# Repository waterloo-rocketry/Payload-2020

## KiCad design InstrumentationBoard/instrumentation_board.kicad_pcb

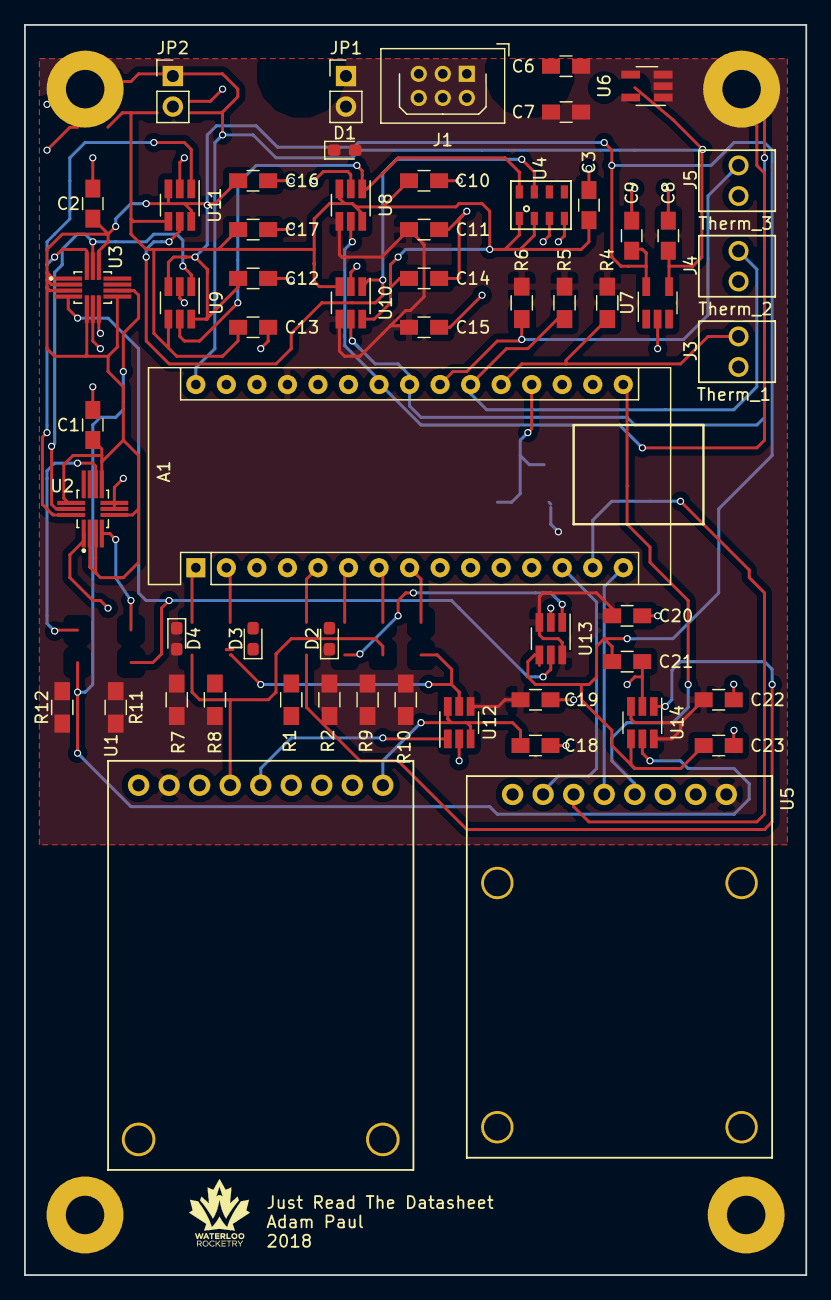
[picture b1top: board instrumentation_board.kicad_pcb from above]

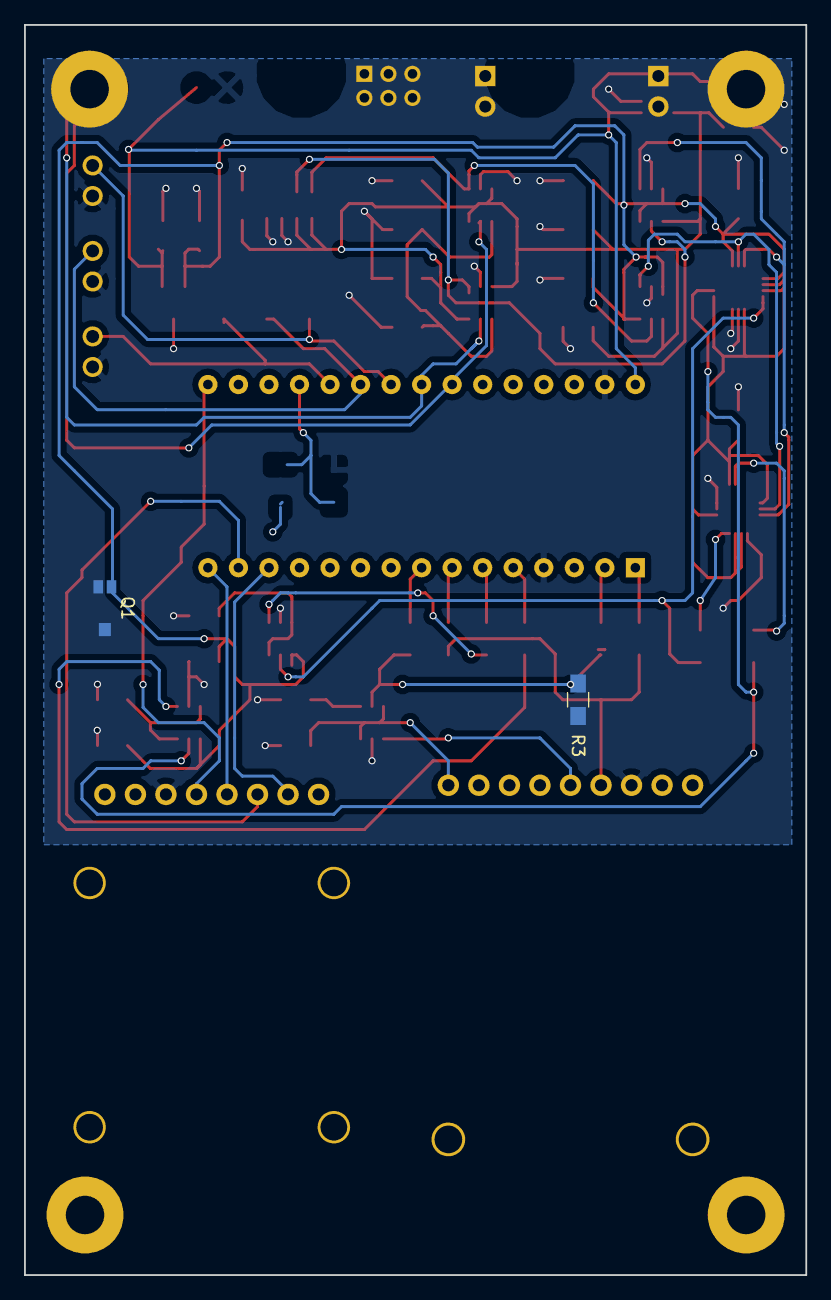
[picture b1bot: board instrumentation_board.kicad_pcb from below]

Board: 2 copper layers, 65.0 x 104.0 mm, 59 parts (2 on the bottom side), 39 nets.

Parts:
A1: Arduino_Nano
C1, C2, C3: 100nF; C_0805_HandSoldering
C6, C7: C; C_0805_HandSoldering
C8: 0.1uF; C_0805_HandSoldering
C9: 0.47uF; C_0805_HandSoldering
C10, C11, C12, C13, C14, C15, C16, C17, C18, C19, C20, C21, C22, C23: .1uF; C_0805_HandSoldering
D1, D2, D3, D4: LED; D_0603_1608Metric_Pad1.05x0.95mm_HandSolder
J1: Conn_01x06; Harwin_LTek-Male_2x03_P2.00mm_Vertical
J3, J4, J5: Conn_01x02; molex_kk_22-23-2021
JP1, JP2: Jumper; PinHeader_1x02_P2.54mm_Vertical
Q1: TEMT6000X01
R1, R2, R3, R7: 120; R_0805_HandSoldering
R4, R5, R6: R; R_0805_HandSoldering
R8, R9, R10: 0; R_0805_HandSoldering
R11, R12: 470; R_0805_HandSoldering
U1: LSM303AGR; gps746
U2, U3: LSM6DS3HTR; LGA-14
U4: MS5607-02BA03; 8-SMD
U5: MicroSD-ADAFRUIT254; adafruit254
U6: XC6201P302MR-G; SOT-23-5_HandSoldering
U7: TPS71518DCKR; SOT-23-5_HandSoldering
U8, U9, U10, U11, U12, U13, U14: PI4ULS5V201TAEX; SOT-23-6_Handsoldering

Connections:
1.8V: C1.1, C2.1, C7.1, C9.1, C12.1, C16.1, C21.1, C23.1, J1.2, R1.2, U1.2, U1.3, U1.9, U2.2, U2.3, U2.5, U2.8, U2.12, U3.1, U3.2, U3.3, U3.5, U3.8, U3.12, U7.5, U9.3, U9.6, U11.3, U11.6, U13.4, U14.4
3V: C3.1, C10.1, C13.1, C14.1, C17.1, J1.3, R2.2, U4.1, U4.2, U6.5, U8.3, U8.6, U9.4, U10.3, U10.6, U11.4
5V: A1.27, C11.1, C15.1, C19.1, C20.1, C22.1, J1.4, Q1.1, R3.2, R4.1, R5.1, R6.1, U5.1, U8.4, U10.4, U12.4, U13.3, U13.6, U14.3, U14.6
7.4V: C8.1, U6.1, U7.4
/ICShifter7/VccA: C18.1, U12.3, U12.6
/Sheet5ABF9899/THERM_OUT: A1.21, J4.2, R5.2
/Sheet5ABF9899_2/THERM_OUT: A1.20, J3.2, R4.2
/Sheet5ABF9899_3/THERM_OUT: A1.22, J5.2, R6.2
GND: A1.4, A1.29, C1.2, C2.2, C3.2, C6.2, C7.2, C8.2, C9.2, C10.2, C11.2, C12.2, C13.2, C14.2, C15.2, C16.2, C17.2, C18.2, C19.2, C20.2, C21.2, C22.2, C23.2, D1.1, D2.1, D3.1, D4.1, J1.1, J3.1, J4.1, J5.1, U1.6, U1.8, U2.1, U2.6, U2.7, U3.6, U3.7, U4.3, U4.4, U5.3, U6.2, U7.2, U8.2, U9.2, U10.2, U11.2, U12.2, U13.2, U14.2
GPS_OUT: R8.1, R10.1, U12.5
INIT_MAG: A1.12, U1.7
INT0_1.8V: R11.1, U3.4, U13.5
INT0_5V: JP2.1, U13.1
INT1_1.8V: R12.2, U3.9, U14.5
INT1_5V: JP1.2, U14.1
MISO: A1.15, U5.5
MOSI: A1.14, U5.6
unnamed: A1.2, R8.2
unnamed: A1.5, JP1.1
unnamed: A1.6, JP2.2
unnamed: A1.7, R9.2
unnamed: A1.8, R10.2
unnamed: A1.11, R7.2
unnamed: C6.1, U1.5
unnamed: D1.2, R1.1
unnamed: D2.2, R2.1
unnamed: D3.2, R3.1
unnamed: D4.2, R7.1
unnamed: R11.2, U2.4
unnamed: R12.1, U2.9
SCL_1.8V: U1.1, U2.13, U3.13, U9.1
SCL_3V: U4.8, U8.1, U9.5
SCL_5V: A1.24, J1.5, U8.5
SDA_1.8V: U1.4, U2.14, U3.14, U11.1
SDA_3V: U4.7, U10.1, U11.5
SDA_5V: A1.23, J1.6, U10.5
SIG: A1.19, Q1.2
SLK: A1.16, U5.4
SS: A1.13, U5.7

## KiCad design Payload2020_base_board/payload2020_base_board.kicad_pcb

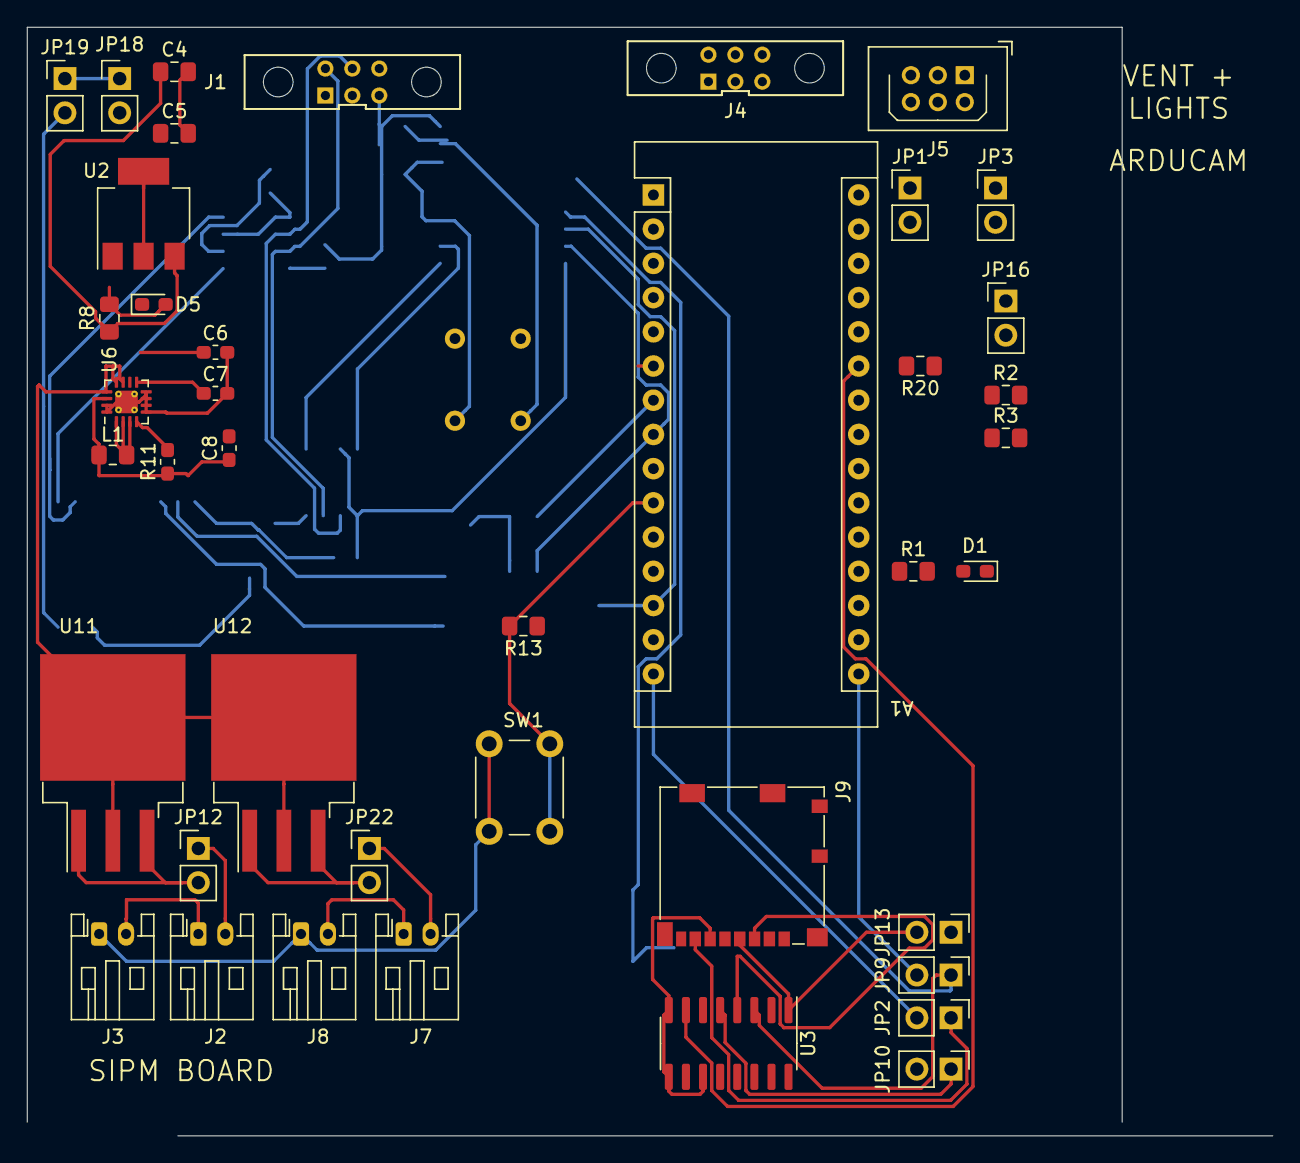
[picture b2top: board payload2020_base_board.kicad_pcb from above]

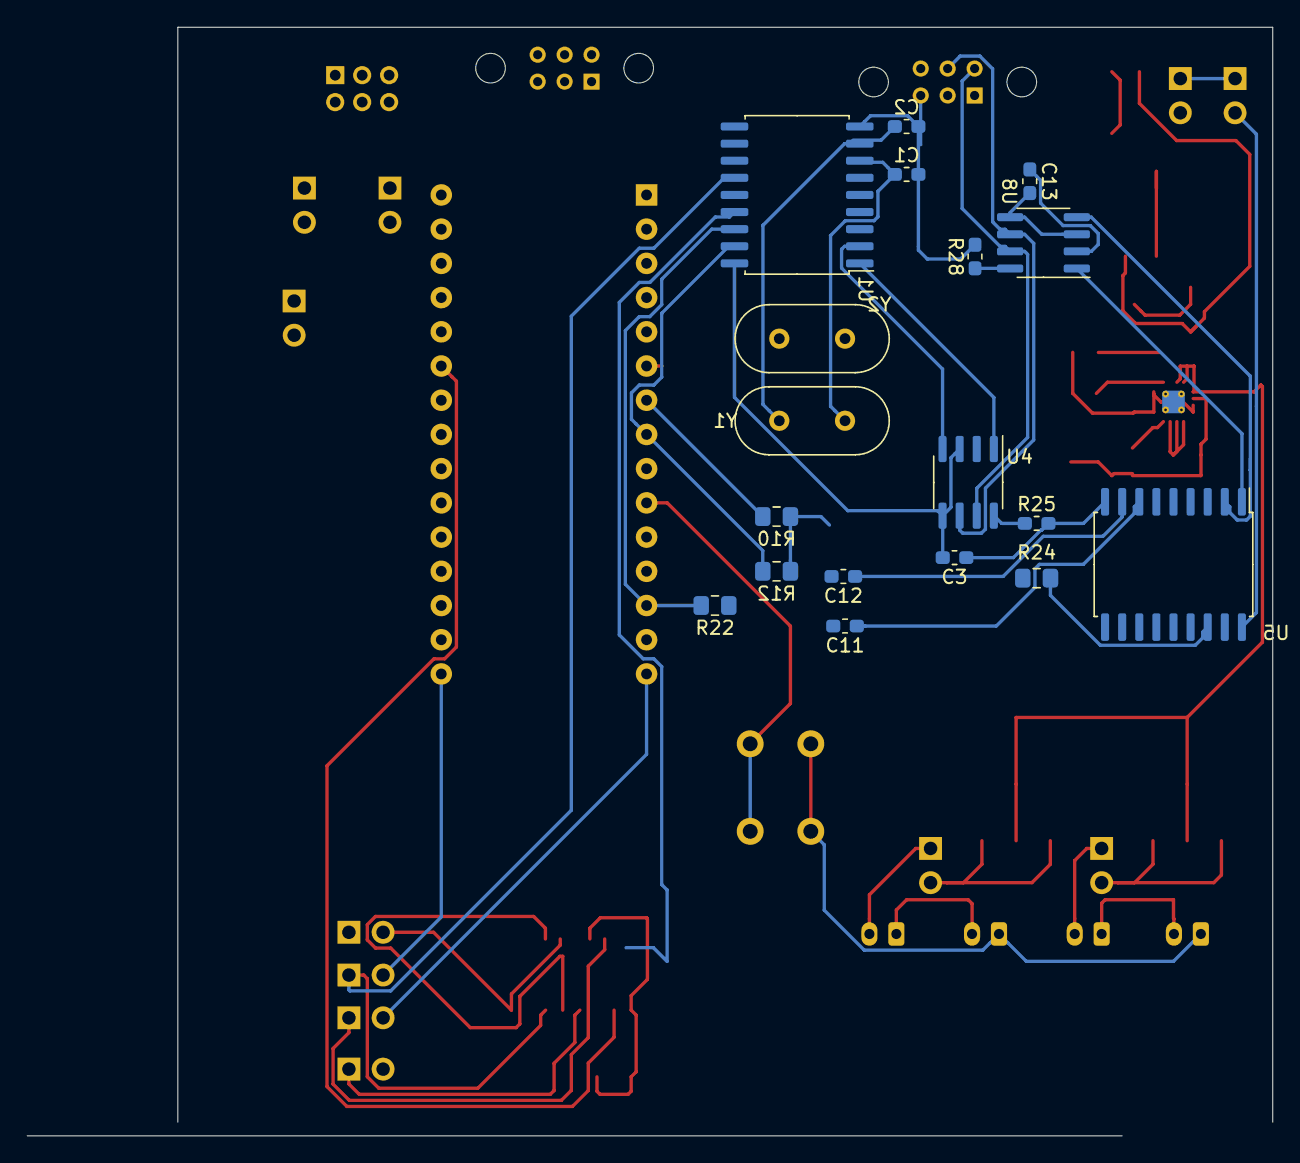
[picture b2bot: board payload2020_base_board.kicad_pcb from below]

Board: 2 copper layers, 92.5 x 82.3 mm, 59 parts (18 on the bottom side), 54 nets.

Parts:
A1: Arduino_Nano_v3.x; Arduino_Nano
C1, C2, C11, C12: 22pF; C_0603_1608Metric_Pad1.05x0.95mm_HandSolder
C3, C6, C13: 10uF; C_0603_1608Metric_Pad1.05x0.95mm_HandSolder
C4: 100nF; C_0805_2012Metric_Pad1.15x1.40mm_HandSolder
C5: 10uF; C_0805_2012Metric_Pad1.15x1.40mm_HandSolder
C7: 3.3nF; C_0603_1608Metric_Pad1.05x0.95mm_HandSolder
C8: 22uF; C_0603_1608Metric_Pad1.05x0.95mm_HandSolder
D1, D5: LED; D_0603_1608Metric_Pad1.05x0.95mm_HandSolder
J1: Conn_01x05; connector_Harwin_M80-5000642_vertical
J2, J3, J7, J8: Conn_01x02; JST_PH_S2B-PH-K_1x02_P2.00mm_Horizontal
J4: Conn_01x06; connector_Harwin_M80-5000642
J5: Conn_01x06; Harwin_LTek-Male_2x03_P2.00mm_Vertical
J9: Micro_SD_Card; microSD_HC_Molex_104031-0811
JP1, JP2, JP3, JP9, JP10, JP12, JP13, JP16, JP18, JP19, JP22: Jumper; PinHeader_1x02_P2.54mm_Vertical
L1: 2.2uH; L_0805_2012Metric_Pad1.15x1.40mm_HandSolder
R1, R8: 120; R_0805_2012Metric_Pad1.15x1.40mm_HandSolder
R2, R3, R10, R12, R13, R20, R22, R24: 10k; R_0805_2012Metric_Pad1.15x1.40mm_HandSolder
R11: 100k; R_0603_1608Metric_Pad1.05x0.95mm_HandSolder
R25, R28: 4.7k; R_0603_1608Metric_Pad1.05x0.95mm_HandSolder
SW1: SW_Push; SW_PUSH_6mm
U1, U5: MCP2515-xSO; SOIC-18W_7.5x11.6mm_P1.27mm
U2: LD1117S33TR_SOT223; SOT-223-3_TabPin2
U3: CD74HC4050; SOIC-16_3.9x9.9mm_P1.27mm
U4, U8: MCP2562-E-SN; SOIC-8_3.9x4.9mm_P1.27mm
U6: TPS62143; VQFN-16-1EP_3x3mm_P0.5mm_EP1.68x1.68mm_ThermalVias
U11, U12: SM74611; TO-263-3_TabPin4
Y1, Y2: 16MHz; Crystal_HC49-4H_Vertical

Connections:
+3V3: C5.1, JP13.1, U2.2
+5V: C4.1, J5.3, JP16.1, R2.1, R3.1, R8.1, R10.1, R12.1, R13.1, R20.1, R22.1, R24.1, U2.3
/CAN HW/CANH: J1.4, U4.7, U8.7
/CAN HW/CANL: J1.5, U4.6, U8.6
/CAN HW/CAN_5v: C3.2, JP18.2, U1.18, U4.3, U4.5
/CAN HW/~INT: A1.7, R10.2, U1.12
/CAN HW/~RESET: A1.8, R12.2, U1.17
/MISO1: J9.7, JP2.1, U1.15
/MOSI1: JP10.1, U1.14, U3.5
/PG: A1.6, R11.2, U6.4
/SCK1: JP9.1, U1.13, U3.3
/SCL: A1.24, JP1.1
/SDA: A1.23, JP3.1
/SS1: A1.25, R20.2, U3.7
/SS3: A1.13, R22.2, U1.16
/SS5: R24.2, U5.16
/battery_management/VIN: C6.1, U6.10, U6.11, U6.12, U6.13, U11.2, U11.4, U12.2, U12.4
/battery_management/VOUT: C8.1, L1.2, R11.1, U6.14
/sheet5E2B166E/CAN_5v: C13.2, JP19.2, U5.18, U8.3, U8.5
GND: A1.4, A1.29, C1.2, C2.2, C3.1, C4.2, C5.2, C6.2, C7.2, C8.2, C11.2, C12.2, C13.1, D1.1, D5.1, J1.3, J3.1, J4.5, J4.6, J5.6, J8.1, J9.6, J9.9, R25.2, R28.2, SW1.1, U1.9, U2.1, U3.8, U3.9, U3.11, U3.14, U4.2, U5.9, U6.5, U6.6, U6.7, U6.8, U6.15, U6.16, U6.17, U8.2
unnamed: A1.10, R13.2, SW1.2
unnamed: A1.14, JP10.2
unnamed: A1.15, JP2.2
unnamed: A1.16, JP9.2
unnamed: A1.19, R1.2
unnamed: A1.22, J4.3, J4.4
unnamed: C1.1, U1.7, Y1.1
unnamed: C2.1, U1.8, Y1.2
unnamed: C7.1, U6.9
unnamed: C11.1, U5.7, Y2.1
unnamed: C12.1, U5.8, Y2.2
unnamed: D1.2, R1.1
unnamed: D5.2, R8.2
unnamed: J2.1, J3.2
unnamed: J2.2, JP12.1
unnamed: J4.1, J4.2, JP16.2
unnamed: J5.1, JP3.2, R3.2
unnamed: J5.2, JP1.2, R2.2
unnamed: J7.1, J8.2
unnamed: J7.2, JP22.1
unnamed: J9.2, U3.6
unnamed: J9.3, U3.4
unnamed: J9.4, JP13.2, U3.1
unnamed: J9.5, U3.2
unnamed: JP12.2, U11.1, U11.3
unnamed: JP22.2, U12.1, U12.3
unnamed: L1.1, U6.1, U6.2, U6.3
unnamed: R25.1, U4.8
unnamed: R28.1, U8.8
unnamed: U1.1, U4.1
unnamed: U1.2, U4.4
unnamed: U5.1, U8.1
unnamed: U5.2, U8.4
SLEEP_5V: A1.27, JP18.1, JP19.1

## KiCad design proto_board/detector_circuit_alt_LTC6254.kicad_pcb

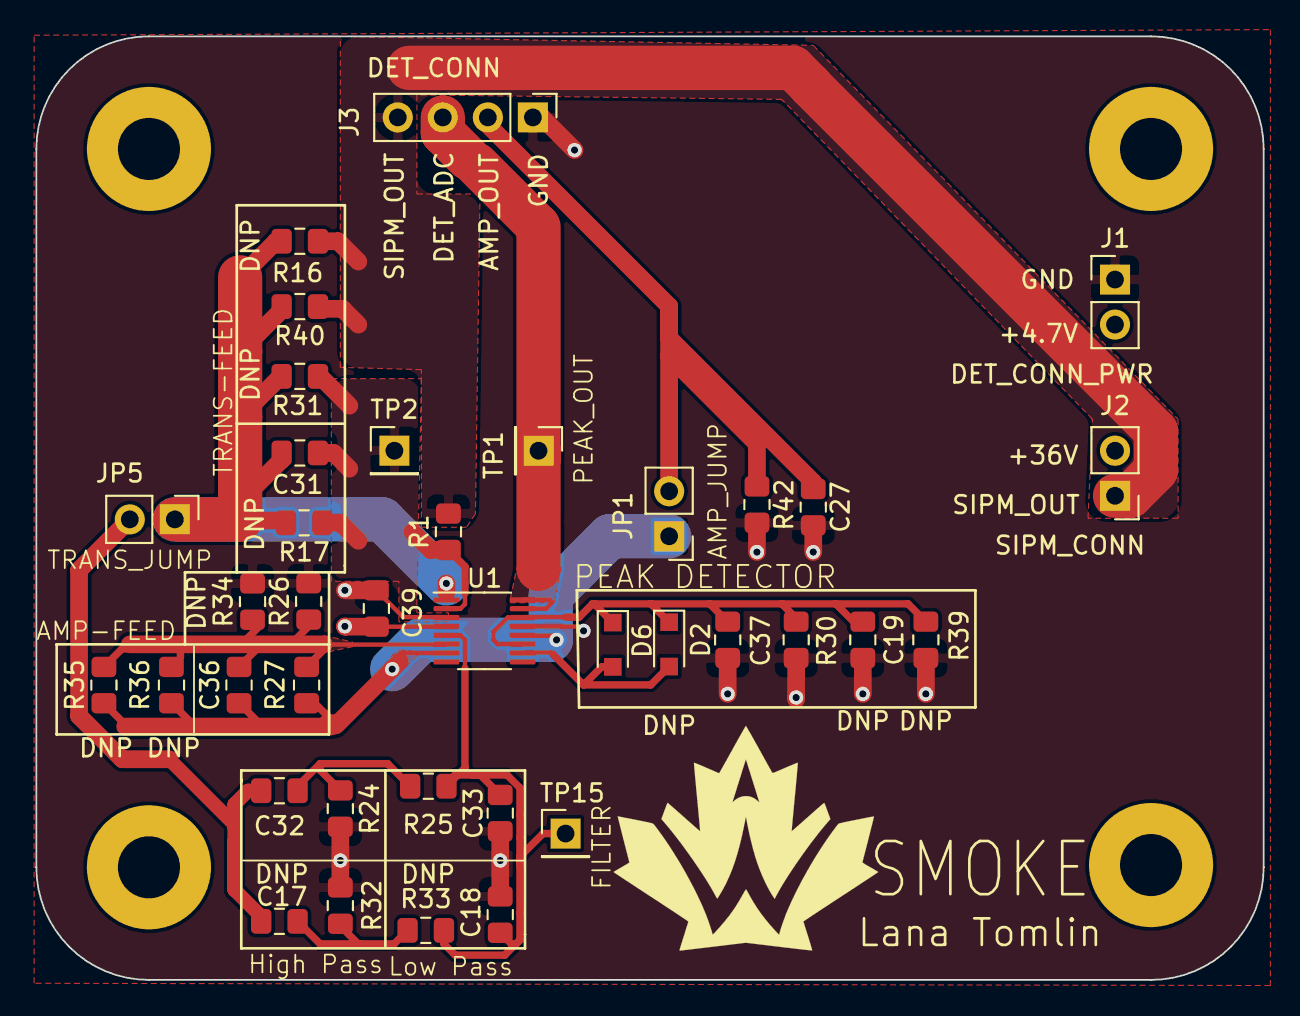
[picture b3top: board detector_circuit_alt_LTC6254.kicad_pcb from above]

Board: 4 copper layers, 69.2 x 53.2 mm, 38 parts (0 on the bottom side), 15 nets.

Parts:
C17, C18, C19: DNP; C_0805_2012Metric_Pad1.15x1.40mm_HandSolder
C27, C37: 2.2n; C_0805_2012Metric_Pad1.15x1.40mm_HandSolder
C31, C33: 1n; C_0805_2012Metric_Pad1.15x1.40mm_HandSolder
C32: 10n; C_0805_2012Metric_Pad1.15x1.40mm_HandSolder
C36: 470p; C_0805_2012Metric_Pad1.15x1.40mm_HandSolder
C39: 0.1u; C_0805_2012Metric_Pad1.15x1.40mm_HandSolder
D2, D6: CUS08F30H3FCT-ND; D_SOD-323_HandSoldering
J1: DET_CONN_PWR; PinHeader_1x02_P2.54mm_Vertical
J2: SIPM_CONN; PinHeader_1x02_P2.54mm_Vertical
J3: DET_CONN; PinHeader_1x04_P2.54mm_Vertical
JP1: AMP_JUMP; PinHeader_1x02_P2.54mm_Vertical
JP5: TRANS_JUMP; PinHeader_1x02_P2.54mm_Vertical
R1: 1; R_0805_2012Metric_Pad1.15x1.40mm_HandSolder
R16, R17, R31, R32, R33, R34, R35, R36, R39: DNP; R_0805_2012Metric_Pad1.15x1.40mm_HandSolder
R24, R26: 100; R_0805_2012Metric_Pad1.15x1.40mm_HandSolder
R25, R40: 150; R_0805_2012Metric_Pad1.15x1.40mm_HandSolder
R27: 330; R_0805_2012Metric_Pad1.15x1.40mm_HandSolder
R30, R42: 1M; R_0805_2012Metric_Pad1.15x1.40mm_HandSolder
TP1: PEAK_OUT; PinHeader_1x01_P2.54mm_Vertical
TP2: SIPM; PinHeader_1x01_P2.54mm_Vertical
TP15: FILTER; PinHeader_1x01_P2.54mm_Vertical
U1: LTC6254; MSOP-16_3x4.039mm_P0.5mm

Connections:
+4.7V: C39.1, J1.2, U1.4
/AMP_OUT: C27.1, J3.2, JP1.2, R42.1
/DET_ADC: J3.3, TP1.1, U1.15, U1.16
/Filter_IN: C17.2, C32.2, JP5.2
/SIPM_OUT: J2.1, J3.4, R1.2, R16.2, R40.2
GND: C18.1, C19.2, C27.2, C33.1, C37.2, C39.2, J1.1, J3.1, R24.2, R26.2, R30.2, R32.2, R34.1, R39.2, R42.2, U1.3, U1.13
unnamed: C17.1, R32.1, R33.2
unnamed: C18.2, C33.2, R25.1, R33.1, TP15.1, U1.5
unnamed: C19.1, C37.1, D2.1, D6.1, R30.1, R39.1, U1.11, U1.14
unnamed: C31.1, JP5.1, R16.1, R17.1, R31.1, R40.1, U1.1
unnamed: C31.2, R1.1, R17.2, R31.2, TP2.1, U1.2
unnamed: C32.1, R24.1, R25.2
unnamed: C36.1, JP1.1, R27.1, R35.1, R36.1, U1.7, U1.12
unnamed: C36.2, R26.1, R27.2, R34.2, R35.2, R36.2, U1.6
unnamed: D2.2, D6.2, U1.10

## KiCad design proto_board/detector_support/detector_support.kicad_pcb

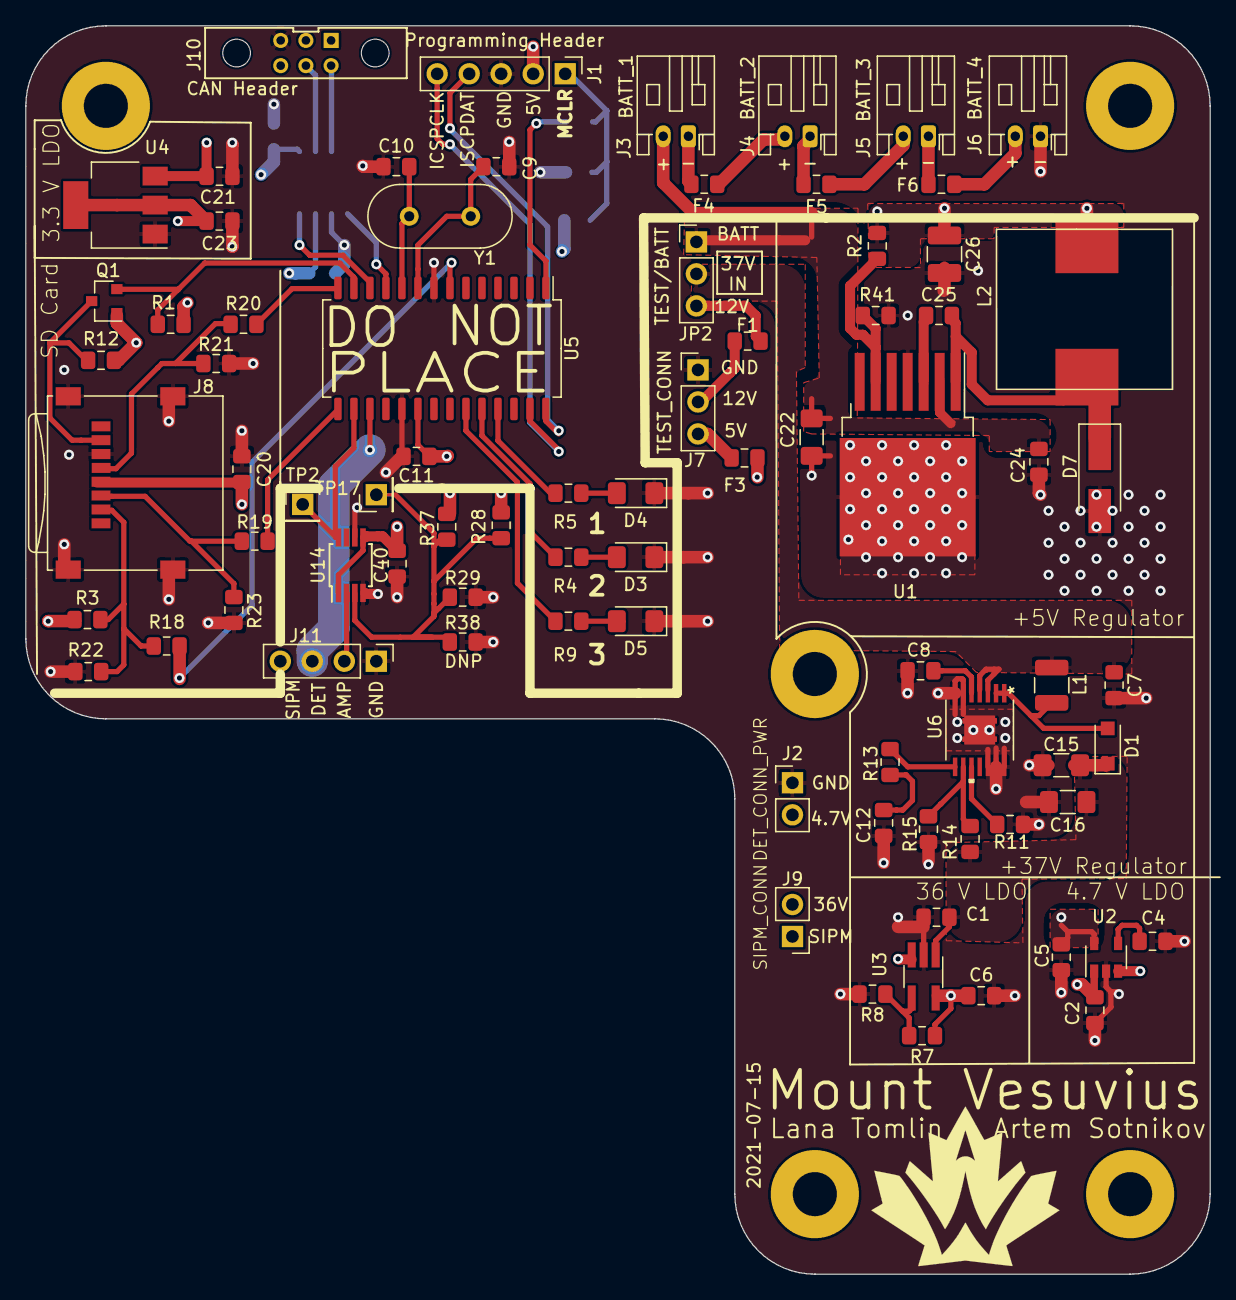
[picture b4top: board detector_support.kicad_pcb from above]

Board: 4 copper layers, 94.0 x 99.1 mm, 86 parts (0 on the bottom side), 55 nets.

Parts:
C1, C2, C5, C21, C23, C24: 1u; C_0805_2012Metric_Pad1.15x1.40mm_HandSolder
C3, C40: 0.1u; C_0805_2012Metric_Pad1.15x1.40mm_HandSolder
C4, C25: 10n; C_0805_2012Metric_Pad1.15x1.40mm_HandSolder
C6: 0.5u; C_0805_2012Metric_Pad1.15x1.40mm_HandSolder
C7: 10u; C_0805_2012Metric_Pad1.15x1.40mm_HandSolder
C8: 47n; C_0805_2012Metric_Pad1.15x1.40mm_HandSolder
C9, C10: 26pF; C_0805_2012Metric_Pad1.15x1.40mm_HandSolder
C11, C13, C14: 0.1uF; C_0805_2012Metric_Pad1.15x1.40mm_HandSolder
C12: 1.5n; C_0805_2012Metric_Pad1.15x1.40mm_HandSolder
C15, C16: 10u; C_1206_3216Metric_Pad1.42x1.75mm_HandSolder
C20: 4.7uF; C_0805_2012Metric_Pad1.15x1.40mm_HandSolder
C22: 4.7u; C_1206_3216Metric_Pad1.42x1.75mm_HandSolder
C26: 56u; C_1210_3225Metric_Pad1.42x2.65mm_HandSolder
D1: 570mV 1a; D_SOD-123F
D3: 156120RS75000; D_1206_3216Metric_Pad1.42x1.75mm_HandSolder
D4: 150120BS75000; D_1206_3216Metric_Pad1.42x1.75mm_HandSolder
D5: QBLP650-IW; D_1206_3216Metric_Pad1.42x1.75mm_HandSolder
D7: D; D_SMA_Handsoldering
F1, F3, F4, F5, F6: 400ma; Fuse_0805_2012Metric_Pad1.15x1.40mm_HandSolder
J1: Programming Header; PinHeader_1x05_P2.54mm_Vertical
J2: DET_CONN_PWR; PinHeader_1x02_P2.54mm_Vertical
J3: BATT_1; JST_PH_S2B-PH-K_1x02_P2.00mm_Horizontal
J4: BATT_2; JST_PH_S2B-PH-K_1x02_P2.00mm_Horizontal
J5: BATT_3; JST_PH_S2B-PH-K_1x02_P2.00mm_Horizontal
J6: BATT_4; JST_PH_S2B-PH-K_1x02_P2.00mm_Horizontal
J7: TEST_CONN; PinHeader_1x03_P2.54mm_Vertical
J8: 693072010801; microSD_Molex_WM6698CT-ND
J9: SIPM_CONN; PinHeader_1x02_P2.54mm_Vertical
J10: Conn_01x06_Female; connector_Harwin_M80-5000642
J11: DET_CONN; PinHeader_1x04_P2.54mm_Vertical
JP2: TEST/BATT; PinHeader_1x03_P2.54mm_Vertical
L1: 33u; L_1210_3225Metric
L2: 15u; 732-3880-1-ND
Q1: BSS138; SOT-23
R1, R3, R10, R12: 10k; R_0805_2012Metric_Pad1.15x1.40mm_HandSolder
R2: 20; R_0805_2012Metric_Pad1.15x1.40mm_HandSolder
R4, R5, R9, R41: 330; R_0805_2012Metric_Pad1.15x1.40mm_HandSolder
R6: 100; R_0805_2012Metric_Pad1.15x1.40mm_HandSolder
R7, R28: 100k; R_0805_2012Metric_Pad1.15x1.40mm_HandSolder
R8: 3.5k; R_0805_2012Metric_Pad1.15x1.40mm_HandSolder
R11: 85.4k; R_0805_2012Metric_Pad1.15x1.40mm_HandSolder
R13: 18.2k; R_0805_2012Metric_Pad1.15x1.40mm_HandSolder
R14: 470k; R_0805_2012Metric_Pad1.15x1.40mm_HandSolder
R15: 16.2k; R_0805_2012Metric_Pad1.15x1.40mm_HandSolder
R18, R19, R20: 34k; R_0805_2012Metric_Pad1.15x1.40mm_HandSolder
R21, R22, R23: 66k; R_0805_2012Metric_Pad1.15x1.40mm_HandSolder
R29: 15k; R_0805_2012Metric_Pad1.15x1.40mm_HandSolder
R37, R38: DNP; R_0805_2012Metric_Pad1.15x1.40mm_HandSolder
TP2: INTERRUPT; PinHeader_1x01_P2.54mm_Vertical
TP17: COMP_BIAS; PinHeader_1x01_P2.54mm_Vertical
U1: LM22678TJ-5.0_NOPB; TO-263-7_TabPin4
U2: LD3985M47R_SOT23; SOT-23-5
U3: LT3014IS5#TRMPBF; TSOT-23-5_HandSoldering
U4: AP2114H-3.3TRG1; SOT-223
U5: PIC18LF26K83; SOIC-28W_7.5x18.7mm_P1.27mm
U6: TPS61175QPWPRQ1; TPS61175_Q1_Footprint
U10: MCP2562-E/SN; SOIC-8_3.9x4.9mm_P1.27mm
U14: LT1711xMS8; MSOP-8_3x3mm_P0.65mm
Y1: 12MHz; Crystal_HC49-4H_Vertical

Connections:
+3V3: C20.1, C23.1, J8.4, Q1.1, R3.1, R12.1, U4.2, U4.4
+4.7V: C5.1, J2.2, U2.5
+5V: C2.1, C11.2, C13.1, C14.1, C21.2, C26.1, C40.1, F3.1, J1.2, L2.2, R1.1, R2.1, R10.1, R28.1, R37.1, U2.1, U2.3, U3.3, U4.3, U5.20, U10.3, U10.5, U14.1, U14.5
+12V: F1.1, JP2.3
+36V: C6.1, J9.2, R7.1, U3.5
+37V: C1.1, C15.1, C16.1, D1.1, R14.1, U3.1
+BATT: C22.1, C24.1, J3.2, JP2.1, U1.2
/AMP_OUT: J11.2, U14.2
/DET_ADC: J11.3, U5.17
/INTERUPT_OUT: TP2.1, U5.16, U14.8
/Microcontroller [DO NOT PLACE]/CANH: J10.4, U10.7
/Microcontroller [DO NOT PLACE]/CANL: J10.5, U10.6
/Microcontroller [DO NOT PLACE]/CS: R18.2, U5.7
/Microcontroller [DO NOT PLACE]/ICSPCLK: J1.5, U5.27
/Microcontroller [DO NOT PLACE]/ICSPDAT: J1.4, U5.28
/Microcontroller [DO NOT PLACE]/MCLR: C3.1, J1.1, R6.2, R10.2
/Microcontroller [DO NOT PLACE]/MISO: Q1.2, R1.2, R19.2, U5.13, U5.15
/Microcontroller [DO NOT PLACE]/OSC1: C9.1, U5.9, Y1.1
/Microcontroller [DO NOT PLACE]/OSC2: C10.1, U5.10, Y1.2
/Microcontroller [DO NOT PLACE]/PIC_RX: U5.12, U10.4
/Microcontroller [DO NOT PLACE]/PIC_TX: U5.11, U10.1
/Microcontroller [DO NOT PLACE]/SCK: R20.2, U5.14
GND: C1.2, C2.2, C3.2, C4.2, C5.2, C6.2, C7.2, C8.2, C9.2, C10.2, C11.1, C12.2, C13.2, C14.2, C15.2, C16.2, C20.2, C21.1, C22.2, C23.2, C24.2, C26.2, C40.2, D3.1, D4.1, D5.1, D7.2, J1.3, J2.1, J6.1, J7.1, J8.6, J8.9, J10.3, J11.1, R8.2, R11.2, R15.2, R21.2, R22.2, R23.2, R29.2, R38.2, R41.2, U1.4, U2.2, U3.2, U4.1, U5.8, U5.19, U6.6, U6.7, U6.12, U6.13, U6.14, U6.15, U10.2, U10.8, U14.4, U14.6
unnamed: C4.1, U2.4
unnamed: C7.1, JP2.2, L1.2, U6.3, U6.4
unnamed: C8.1, U6.5
unnamed: C12.1, R13.1
unnamed: C25.1, D7.1, L2.1, U1.1
unnamed: C25.2, U1.3
unnamed: D1.2, L1.1, U6.1, U6.2
unnamed: D3.2, R4.2
unnamed: D4.2, R5.2
unnamed: D5.2, R9.2
unnamed: F1.2, J7.2
unnamed: F3.2, J7.3
unnamed: F4.1, J3.1
unnamed: F4.2, J4.2
unnamed: F5.1, J4.1
unnamed: F5.2, J5.2
unnamed: F6.1, J5.1
unnamed: F6.2, J6.2
unnamed: J8.2, R3.2, R18.1, R22.1
unnamed: J8.3, R19.1, R23.1
unnamed: J8.5, R20.1, R21.1
unnamed: J8.7, Q1.3, R12.2
unnamed: R2.2, R41.1, U1.6
unnamed: R4.1, U5.24
unnamed: R5.1, U5.25
unnamed: R6.1, U5.1
unnamed: R7.2, R8.1, U3.4
unnamed: R9.1, U5.23
unnamed: R11.1, U6.10
unnamed: R13.2, U6.8
unnamed: R14.2, R15.1, U6.9
unnamed: R28.2, R29.1, R37.2, R38.1, TP17.1, U14.3
